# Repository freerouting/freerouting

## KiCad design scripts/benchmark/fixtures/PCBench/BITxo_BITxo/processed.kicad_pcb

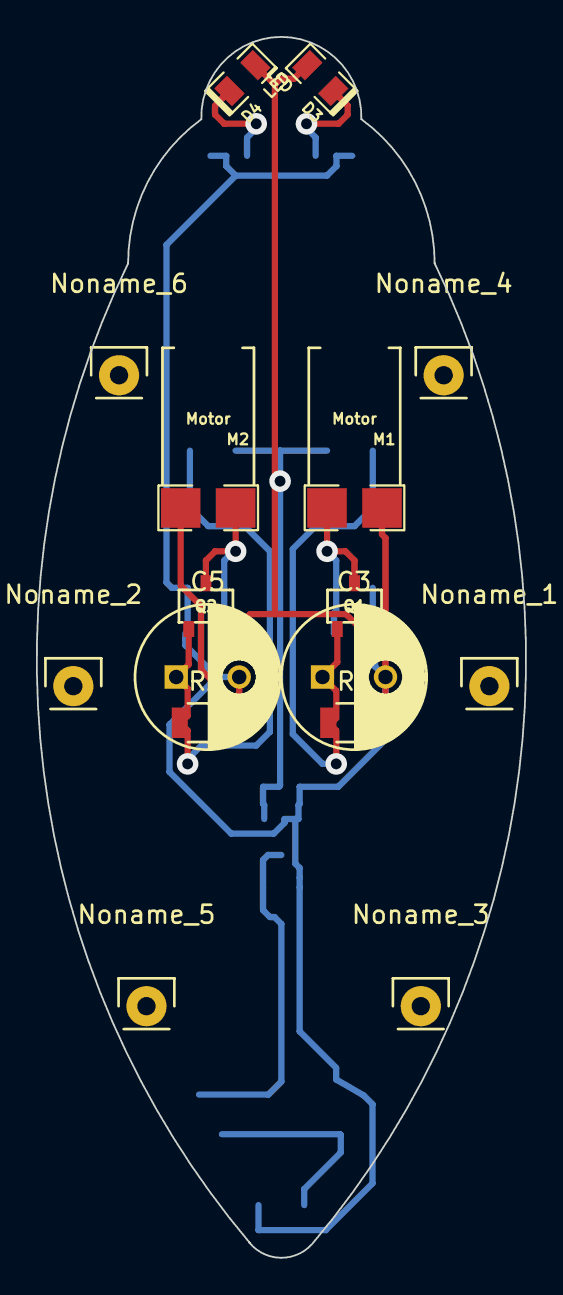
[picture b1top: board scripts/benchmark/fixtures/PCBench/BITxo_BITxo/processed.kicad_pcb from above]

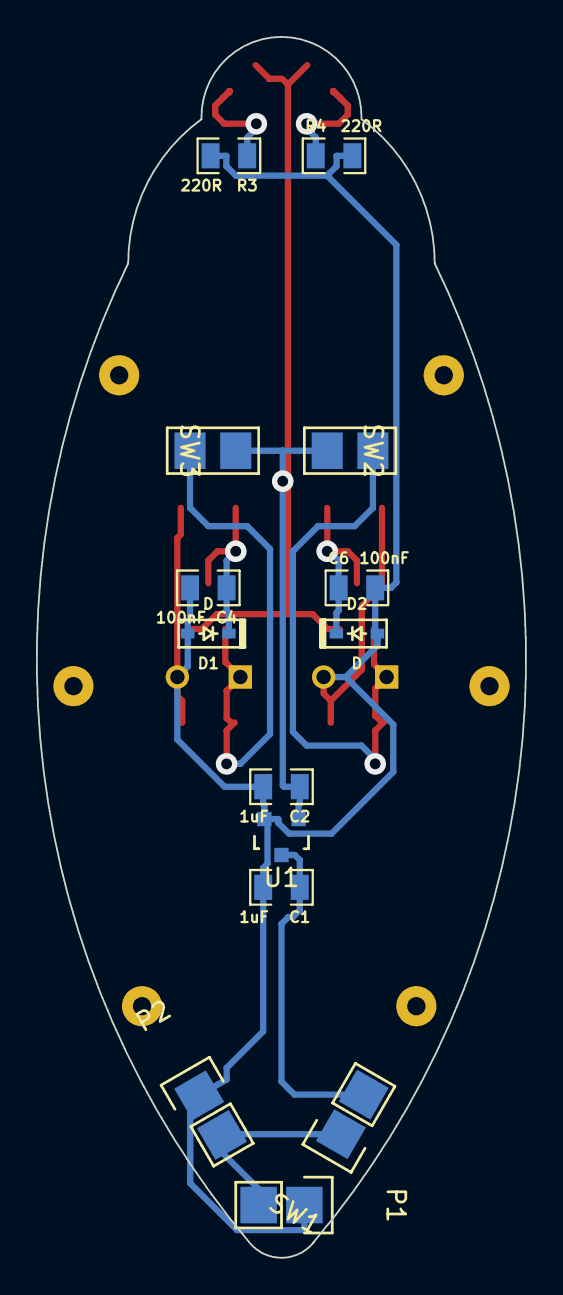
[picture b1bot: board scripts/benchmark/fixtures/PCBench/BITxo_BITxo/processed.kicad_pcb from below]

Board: 2 copper layers, 27.2 x 67.8 mm, 30 parts (14 on the bottom side), 10 nets.

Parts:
C1, C2: 1uF; SMD0805
C3, C5: 1uF; C_Radial_D8_L11.5_P3.5
C4, C6: 100nF; SMD0805
D1, D2: D; SOD-323
D3, D4: LED; SMD0805_LED
M1, M2: Motor; Vibration_motor
Noname_1, Noname_2, Noname_3, Noname_4, Noname_5, Noname_6: Pin_Header_Straight_1x01
P1: Battery Charger; Pads_1x02
P2: Battery; Pads_1x02
Q1, Q2: P-MOSFET; SOT23-5_MOD_PINOUT
R1, R2: 3M3; R_1206
R3, R4: 220R; SMD0805
SW1: ON/OFF; Pads_1x02
SW2, SW3: Endstop; Pads_Endstop
U1: APE8865NL-30-HF-3; SOT-23

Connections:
+3V3: C2.1, D3.2, D4.2, Q1.3, Q2.3, SW2.2, SW3.2, U1.1
+BATT: P1.2, P2.2, SW1.1
GND: C1.2, C2.2, C3.2, C4.2, C5.2, C6.2, D1.2, D2.2, M1.2, M2.1, P1.1, P2.1, R1.2, R2.2, R3.2, R4.2, U1.2
unnamed: C1.1, SW1.2, U1.3
unnamed: C3.1, Q1.2, R1.1, SW2.3
unnamed: C4.1, D1.1, M1.1, Q1.1
unnamed: C5.1, Q2.2, R2.1, SW3.3
unnamed: C6.1, D2.1, M2.2, Q2.1
unnamed: D3.1, R3.1
unnamed: D4.1, R4.1

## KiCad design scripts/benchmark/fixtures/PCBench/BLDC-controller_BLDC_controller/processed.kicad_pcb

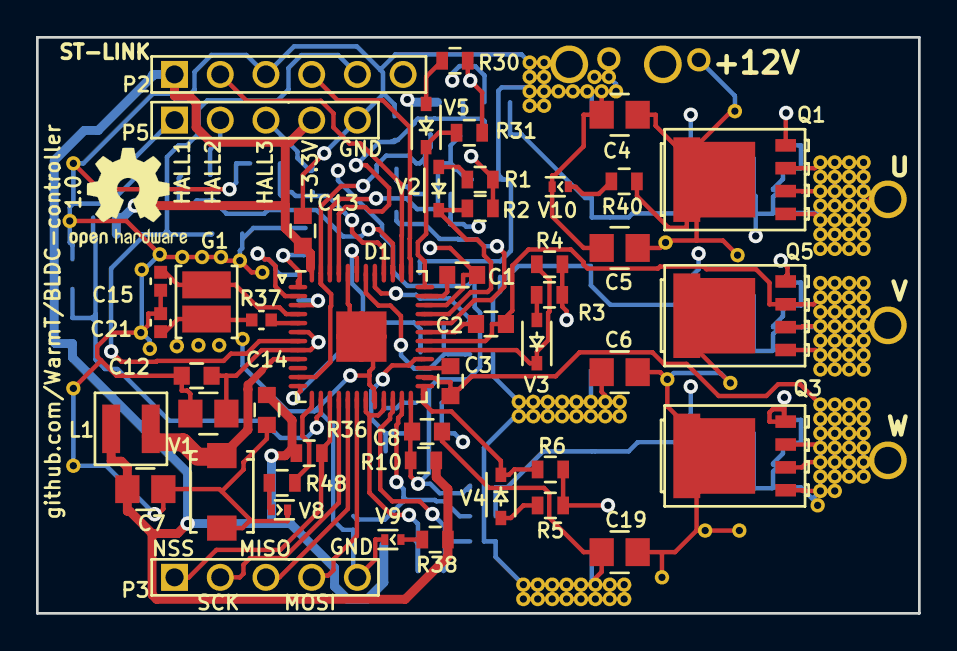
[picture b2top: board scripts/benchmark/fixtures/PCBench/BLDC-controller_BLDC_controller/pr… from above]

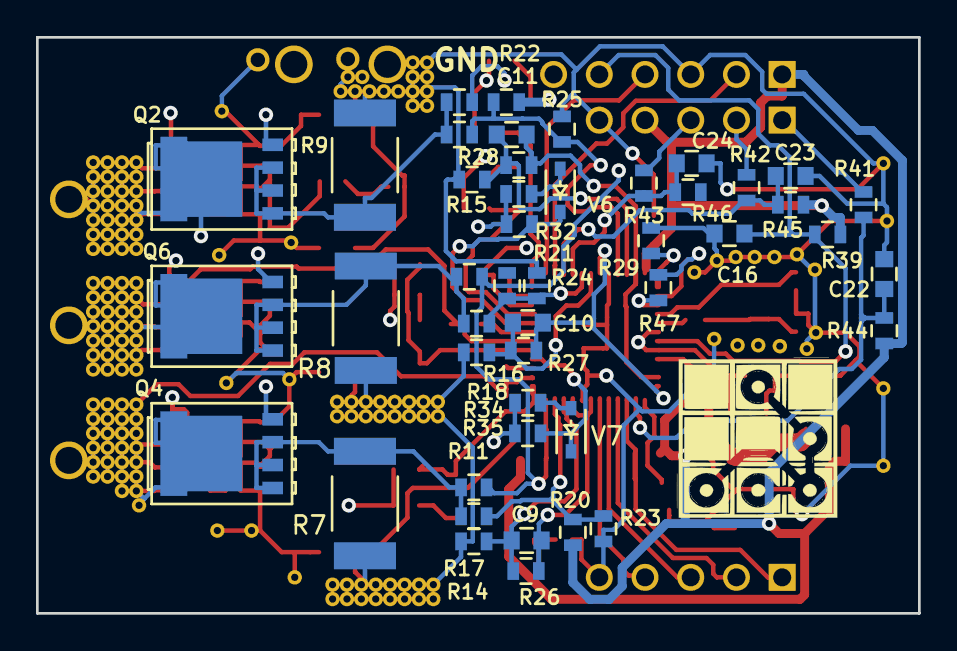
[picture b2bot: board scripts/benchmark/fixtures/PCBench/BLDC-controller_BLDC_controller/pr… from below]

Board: 4 copper layers, 49.0 x 32.0 mm, 92 parts (46 on the bottom side), 64 nets.

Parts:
C1, C2, C3, C12, C13, C14: 100n; C_0603
C4, C5, C6, C17, C19: 220n; C_0805
C7: 47u; C_0805
C8: 1n0; C_0603
C9, C10, C11: 100p; C_0603
C15, C21: 10p; C_0402
C16: 3n3; C_0603
C22, C23, C24: 10p; C_0603
D1: STSPIN32F0; QFN-48-1EP_7x7mm_Pitch0.5mm
G1: NX3225GD; Crystal_3225
L1: SRN3015-220M; BOURNS-SRN3015
P2: CONN_01X06; PINHEAD1-6
P3, P5: CONN_01X05; PINHEAD1-5
Q1, Q2, Q3, Q4, Q5, Q6: PSMN2R0-30YLD; SOT-669_LFPAK56
R1, R3, R5, R30, R32, R34, R47: 10R; R_0603
R2, R4, R6, R31, R33, R35: 62R; R_0603
R7, R8, R9: 0R01; R_2512
R10: 46k4; R_0603
R11, R12, R13, R29, R36, R40: 2k2; R_0603
R14, R15, R16, R41, R42, R43: 1k0; R_0603
R17, R18, R19, R23, R24, R25, R48: 560R; R_0603
R20, R21, R22: 8k2; R_0603
R26, R27, R28: 15k; R_0603
R37: 10R; R_0402_MOST
R38: 330R; R_0603
R39: 39k; R_0603
R44, R45, R46: 10k; R_0603
V1: STPS1L60A; SMA
V2, V3, V4, V5, V6, V7: 4148WS; SOD-323
V8, V9, V10: LED_ALT; LED_0402

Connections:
+3V3: C7.1, C13.1, C14.1, D1.48, L1.1, P2.1, P5.4, R10.2, R20.1, R22.1, R36.1, R38.1, R39.1, R44.1, R45.1
+12V: C4.1, C5.1, C6.1, C12.1, C17.1, C19.1, D1.6, D1.8, Q1.5, Q3.5, Q5.5, R40.1
/HALL1/A+: C22.1, D1.14, R41.1, R44.2
/HALL2/B+: C23.1, D1.39, R42.1, R45.2
/HALL3/Z+: C24.1, D1.40, R43.1, R46.2
/HSU: Q1.4, R1.1, R2.1
/HSV: Q5.4, R3.1, R4.1
/HSW: Q3.4, R5.1, R6.1
/LSU: Q2.4, R30.1, R31.1
/LSV: Q6.4, R32.1, R33.1
/LSW: Q4.4, R34.1, R35.1
/NRST: C16.1, D1.7, P2.5, R39.2
/OC_COMP: C8.1, D1.24, R10.1, R11.2, R12.2, R13.2
/OP1N: C9.2, D1.22, R14.2, R26.2
/OP1P: D1.23, R17.1, R20.2, R23.1
/OP2N: C10.2, D1.42, R16.2, R27.2
/OP2P: D1.41, R18.1, R21.2, R24.1
/OP3N: C11.2, D1.46, R15.2, R28.2
/OP3P: D1.45, R19.1, R22.2, R25.1
/OP4N: D1.2, R47.2
/OP4P: D1.1, R29.1
/OSC_IN: C15.1, D1.4, G1.1
/OUTU: C1.1, D1.34, Q1.1, Q1.2, Q1.3, Q2.5
/OUTV: C2.1, D1.30, Q5.1, Q5.2, Q5.3, Q6.5
/OUTW: C3.1, D1.26, Q3.1, Q3.2, Q3.3, Q4.5
/PA2: D1.13, R48.1
/PA2_LED: R48.2, V8.2
/SPI1_MISO: D1.17, P3.3
/SPI1_MOSI: D1.18, P3.4
/SPI1_NSS: D1.15, P3.1, R36.2
/SPI1_SCK: D1.16, P3.2
/SW: D1.9, L1.2, V1.1
/SWCLK: D1.38, P2.2
/SWDIO: D1.37, P2.4
/U_ADC: C11.1, D1.11, D1.47, R28.1
/VBOOSTU: C1.2, D1.35
/VBOOSTV: C2.2, D1.31
/VBOOSTW: C3.2, D1.27
/V_ADC: C10.1, D1.12, D1.43, R27.1
/W_ADC: C9.1, D1.19, D1.21, R26.1
GND: C4.2, C5.2, C6.2, C7.2, C8.2, C12.2, C13.2, C14.2, C15.2, C16.2, C17.2, C19.2, C21.2, C22.2, C23.2, C24.2, D1.20, D1.44, D1.49, P2.3, P3.5, P5.5, R7.2, R8.2, R9.2, R14.1, R15.1, R16.1, R23.2, R24.2, R25.2, R29.2, V1.2, V8.1, V9.1, V10.1
unnamed: C21.1, G1.2, R37.2
unnamed: D1.3, R47.1
unnamed: D1.5, R37.1
unnamed: D1.25, R6.2, V4.1
unnamed: D1.28, R35.2, V7.1
unnamed: D1.29, R4.2, V3.1
unnamed: D1.32, R33.2, V6.1
unnamed: D1.33, R2.2, V2.1
unnamed: D1.36, R31.2, V5.1
unnamed: P5.1, R41.2
unnamed: P5.2, R42.2
unnamed: P5.3, R43.2
unnamed: R1.2, V2.2
unnamed: R3.2, V3.2
unnamed: R5.2, V4.2
unnamed: R30.2, V5.2
unnamed: R32.2, V6.2
unnamed: R34.2, V7.2
unnamed: R38.2, V9.2
unnamed: R40.2, V10.2
U_SENSE_P: Q2.1, Q2.2, Q2.3, R9.1, R13.1, R19.2
V_SENSE_P: Q6.1, Q6.2, Q6.3, R8.1, R12.1, R18.2
W_SENSE_P: Q4.1, Q4.2, Q4.3, R7.1, R11.1, R17.2

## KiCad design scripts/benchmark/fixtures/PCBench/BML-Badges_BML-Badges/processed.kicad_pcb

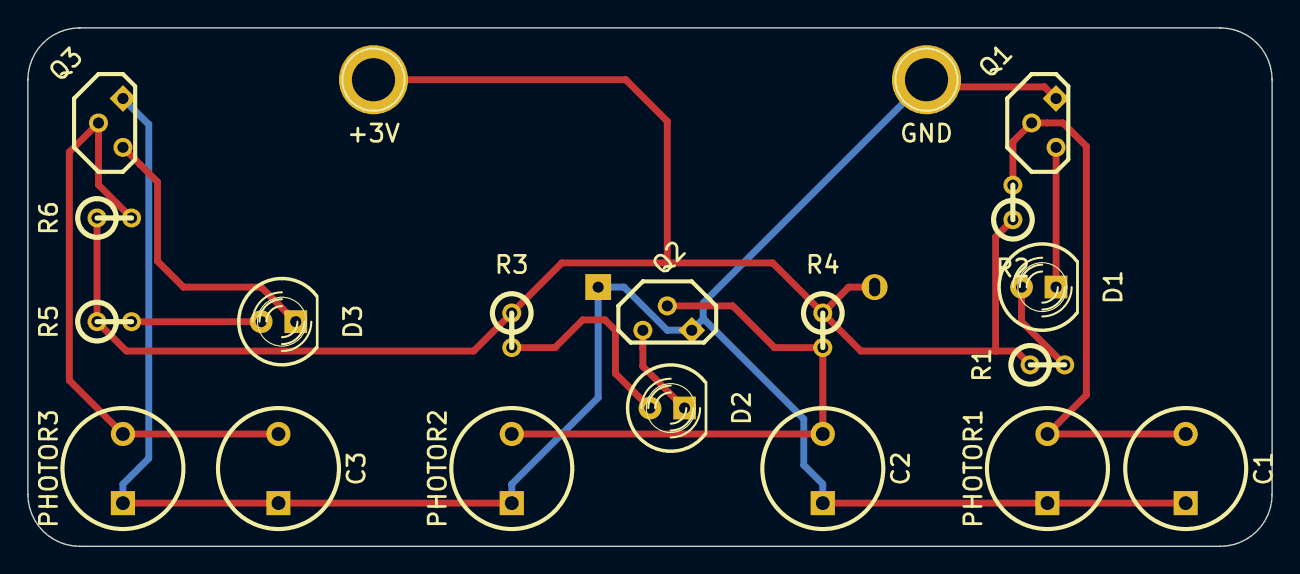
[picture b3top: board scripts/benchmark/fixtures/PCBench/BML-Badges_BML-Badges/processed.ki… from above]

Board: 2 copper layers, 91.4 x 38.1 mm, 21 parts (1 on the bottom side), 11 nets.

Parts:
BT1: 3V; BS-7-CR2032-2
C1, C2, C3: 22uF; C2V8
D1, D2, D3: LED; LED-5MM
P1: +3V; 1pin
P2: GND; 1pin
PHOTOR1, PHOTOR2, PHOTOR3: PHOTOR; LDR
Q1, Q2, Q3: PN2222A; TO92-EBC-num
R1, R3, R5: 330; R1
R2, R4, R6: 100k; R1

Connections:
3V: BT1.1, P1.1, R1.1, R2.1, R3.1, R4.1, R5.1, R6.1
GND: BT1.2, C1.2, C2.2, C3.2, P2.1, PHOTOR1.2, PHOTOR2.2, PHOTOR3.2, Q1.1, Q2.1, Q3.1
unnamed: C1.1, PHOTOR1.1, Q1.2, R2.2
unnamed: C2.1, PHOTOR2.1, Q2.2, R4.2
unnamed: C3.1, PHOTOR3.1, Q3.2, R6.2
unnamed: D1.1, R1.2
unnamed: D1.2, Q1.3
unnamed: D2.1, R3.2
unnamed: D2.2, Q2.3
unnamed: D3.1, R5.2
unnamed: D3.2, Q3.3
